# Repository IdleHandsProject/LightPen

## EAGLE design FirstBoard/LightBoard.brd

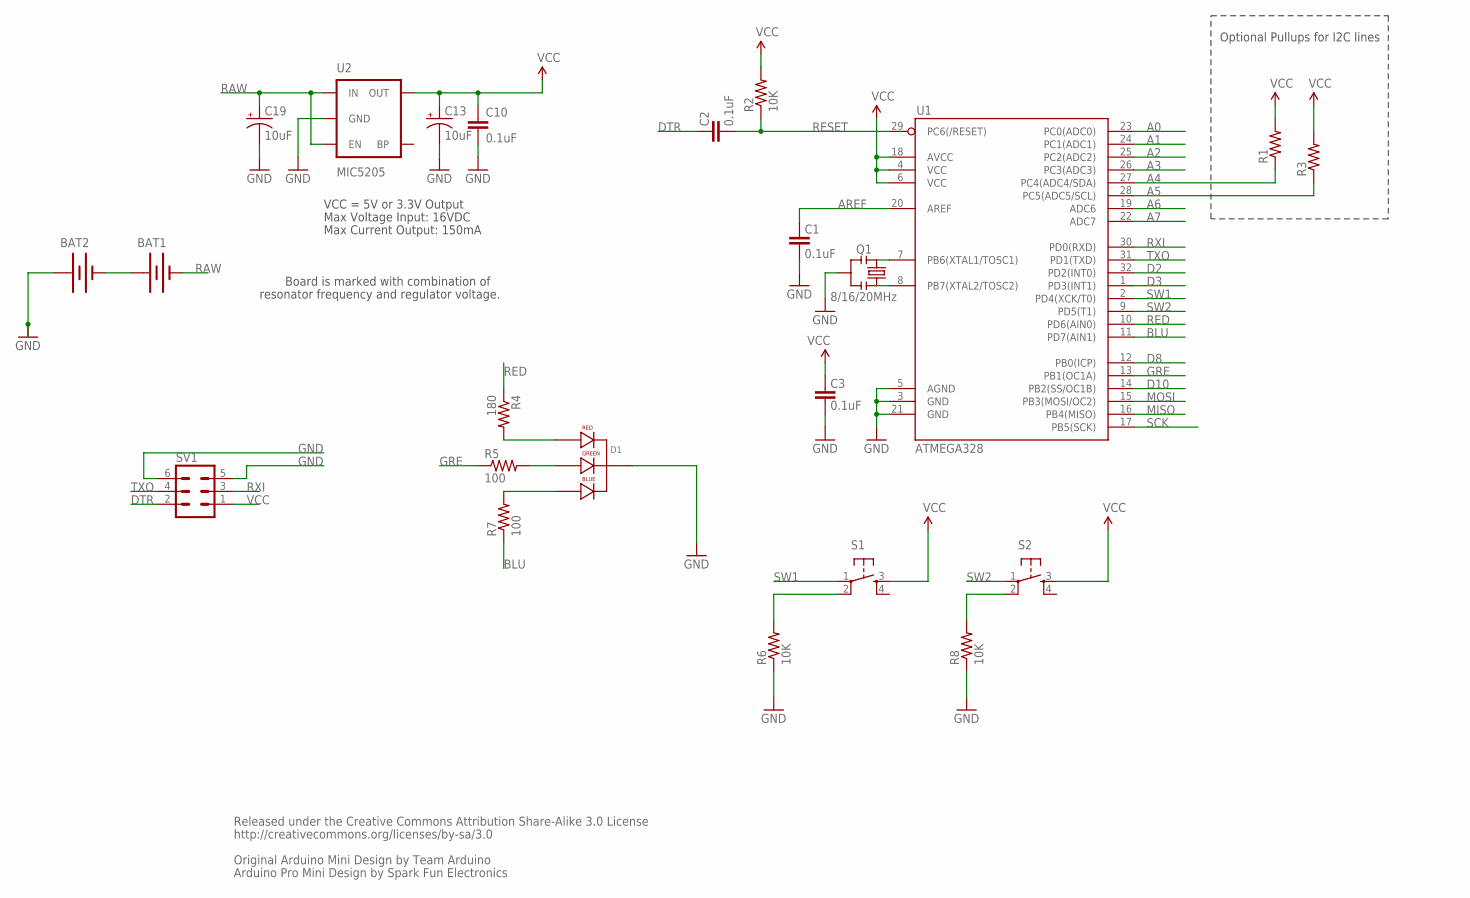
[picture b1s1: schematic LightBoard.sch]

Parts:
BAT1, BAT2: BATTERY12MM; BATTCON_12MM
C1, C2, C3, C10: 0.1uF; 0402-CAP
C13, C19: 10uF; EIA3216
D1: LED-RGB-CC-THRUDIFFUSE; LED-RGB-THRU
Q1: 8/16/20MHz; RESONATOR-SMD
R1, R3: RESISTOR0402-RES; 0402-RES
R2, R6, R8: 10K; 0402-RES
R4: 180; 0402-RES
R5, R7: 100; 0402-RES
S1, S2: TAC_SWITCHPTH; TACTILE-PTH
SV1: MA03-2
U1: ATMEGA328; TQFP32-08
U2: MIC5205; SOT23-5

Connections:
A0: U1.23 (PC0(ADC0))
A1: U1.24 (PC1(ADC1))
A2: U1.25 (PC2(ADC2))
A3: U1.26 (PC3(ADC3))
A4: R1.1, U1.27 (PC4(ADC4/SDA))
A5: R3.1, U1.28 (PC5(ADC5/SCL))
A6: U1.19 (ADC6)
A7: U1.22 (ADC7)
AREF: C1.2, U1.20 (AREF)
BLU: R7.1, U1.11 (PD7(AIN1))
D2: U1.32 (PD2(INT0))
D3: U1.1 (PD3(INT1))
D8: U1.12 (PB0(ICP))
D10: U1.14 (PB2(SS/OC1B))
DTR: C2.2, SV1.2
GND: BAT2.PWR@1 (+), C1.1, C3.1, C10.2, C13.C (-), C19.C (-), D1.2 (CATHODE), Q1.2, R6.1, R8.1, SV1.5, SV1.6, U1.3 (GND), U1.5 (AGND), U1.21 (GND), U2.2 (GND)
GRE: R5.1, U1.13 (PB1(OC1A))
MISO: U1.16 (PB4(MISO))
MOSI: U1.15 (PB3(MOSI/OC2))
unnamed: Q1.1, U1.8 (PB7(XTAL2/TOSC2))
unnamed: Q1.3, U1.7 (PB6(XTAL1/TOSC1))
unnamed: BAT1.PWR@1 (+), BAT2.GND (-)
unnamed: D1.1 (RED_CATHODE), R4.2
unnamed: D1.3 (GREEN_CATHODE), R5.2
unnamed: D1.4 (BLUE_CATHODE), R7.2
unnamed: R6.2, S1.2
unnamed: R8.2, S2.2
RAW: BAT1.GND (-), C19.A (+), U2.1 (IN), U2.3 (EN)
RED: R4.1, U1.10 (PD6(AIN0))
RESET: C2.1, R2.1, U1.29 (PC6(/RESET))
RXI: SV1.3, U1.30 (PD0(RXD))
SCK: U1.17 (PB5(SCK))
SW1: S1.1, U1.2 (PD4(XCK/T0))
SW2: S2.1, U1.9 (PD5(T1))
TXO: SV1.4, U1.31 (PD1(TXD))
VCC: C3.2, C10.1, C13.A (+), R1.2, R2.2, R3.2, S1.3, S2.3, SV1.1, U1.4 (VCC), U1.6 (VCC), U1.18 (AVCC), U2.5 (OUT)

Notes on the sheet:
Released under the Creative Commons Attribution Share-Alike 3.0 License
http://creativecommons.org/licenses/by-sa/3.0
Original Arduino Mini Design by Team Arduino
Arduino Pro Mini Design by Spark Fun Electronics
Max Voltage Input: 16VDC
Max Current Output: 150mA
Board is marked with combination of
resonator frequency and regulator voltage.
VCC = 5V or 3.3V Output
Optional Pullups for I2C lines

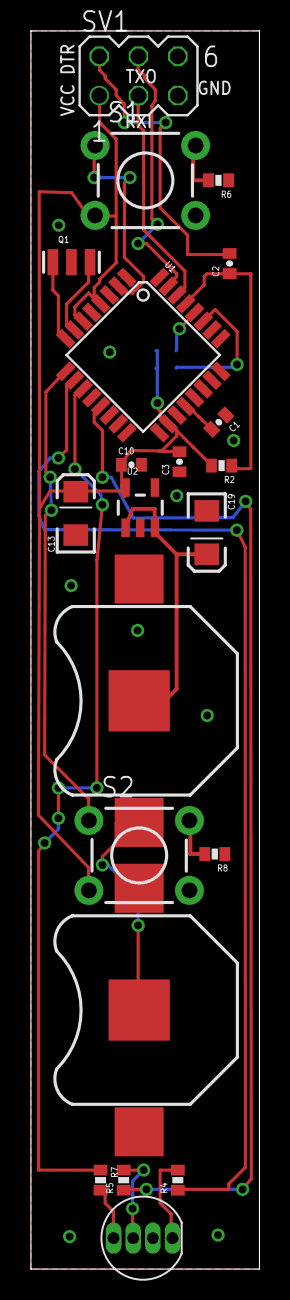
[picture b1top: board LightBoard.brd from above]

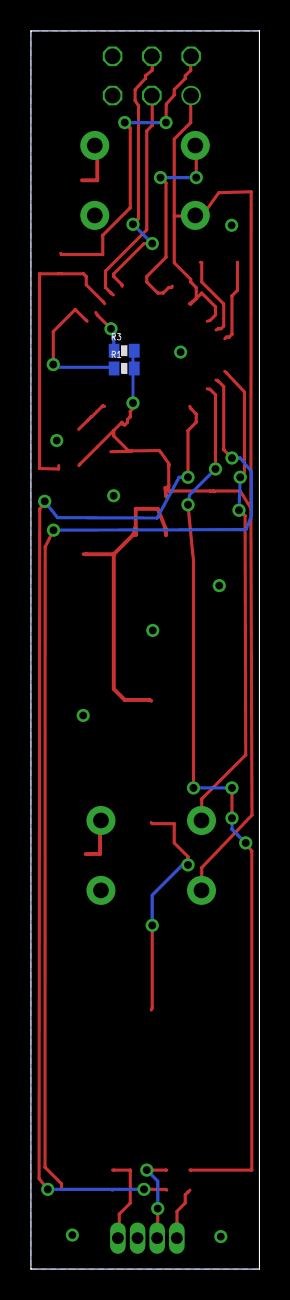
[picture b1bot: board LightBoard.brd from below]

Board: 2 copper layers, 14.8 x 80.1 mm, 23 parts (2 on the bottom side), 23 nets.

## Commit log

2014-02-17 Creation of PCB
    Light pen pcb created and routed, first revision.

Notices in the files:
parts and their libraries:
SparkFun-Electromechanical: Licensing: CC v3.0 Share-Alike You are welcome to use this library for commercial purposes.
